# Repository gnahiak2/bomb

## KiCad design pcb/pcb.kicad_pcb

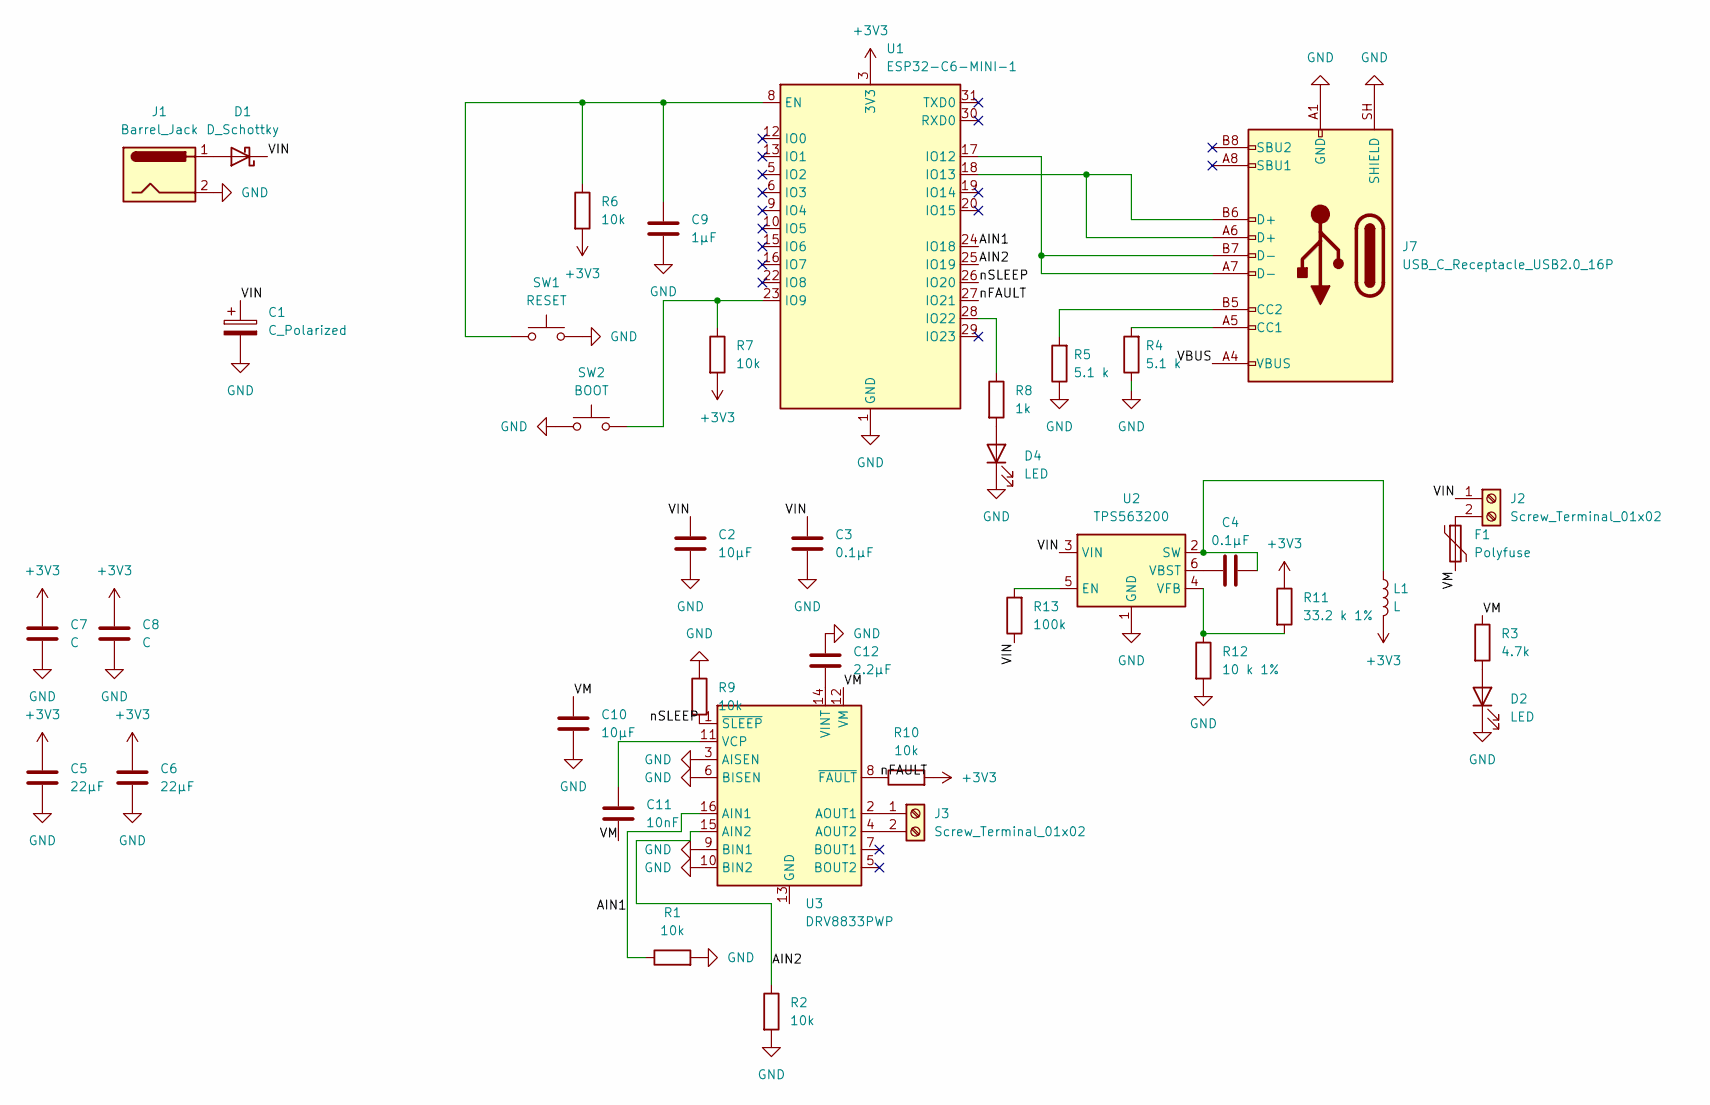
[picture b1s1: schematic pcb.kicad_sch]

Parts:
C1: C_Polarized; CP_Radial_D10.0mm_P5.00mm
C2, C10: 10µF; C_0805_2012Metric
C3, C4: 0.1µF; C_0805_2012Metric
C5, C6: 22µF; C_0805_2012Metric
C7, C8: C; C_0805_2012Metric
C9: 1µF; C_0805_2012Metric
C11: 10nF; C_0805_2012Metric
C12: 2.2µF; C_0805_2012Metric
D1: D_Schottky; D_SMA
D2, D4: LED; LED_0805_2012Metric
F1: Polyfuse; Fuse_1206_3216Metric
J1: Barrel_Jack; BarrelJack_Horizontal
J2, J3: Screw_Terminal_01x02; TerminalBlock_Phoenix_MKDS-1,5-2-5.08_1x02_P5.08mm_Horizont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
J7: USB_C_Receptacle_USB2.0_16P; USB_C_Receptacle_HRO_TYPE-C-31-M-12
L1: L; L_Sunlord_SWPA4030S
R1, R2, R6, R7, R9, R10: 10k; R_0805_2012Metric
R3: 4.7k; R_0805_2012Metric
R4, R5: 5.1 k; R_0805_2012Metric
R8: 1k; R_0805_2012Metric
R11: 33.2 k 1%; R_0805_2012Metric
R12: 10 k 1%; R_0805_2012Metric
R13: 100k; R_0805_2012Metric
SW1: RESET; SW_SPST_TL3342
SW2: BOOT; SW_SPST_TL3342
U1: ESP32-C6-MINI-1
U2: TPS563200; SOT-23-6
U3: DRV8833PWP; HTSSOP-16-1EP_4.4x5mm_P0.65mm_EP3.4x5mm_Mask2.46x2.31mm_The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

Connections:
+3V3: C5.1, C6.1, C7.1, C8.1, L1.2, R6.2, R7.2, R10.2, R11.1, U1.3 (3V3)
/AIN1: R1.1, U1.24 (IO18), U3.16 (AIN1)
/AIN2: R2.1, U1.25 (IO19), U3.15 (AIN2)
/VBUS: J7.A4 (VBUS), J7.A9 (VBUS), J7.B4 (VBUS), J7.B9 (VBUS)
/VIN: C1.1, C2.1, C3.1, D1.1 (K), J2.1, R13.1, U2.3 (VIN)
/VM: C10.1, C11.2, F1.2, R3.1, U3.12 (VM)
/nFAULT: R10.1, U1.27 (IO21), U3.8 (~FAULT)
/nSLEEP: R9.2, U1.26 (IO20), U3.1 (~SLEEP)
GND: C1.2, C2.2, C3.2, C5.2, C6.2, C7.2, C8.2, C9.2, C10.2, C12.1, D2.1 (K), D4.1 (K), J1.2, J7.A1 (GND), J7.A12 (GND), J7.B1 (GND), J7.B12 (GND), J7.SH (SHIELD), R1.2, R2.2, R4.1, R5.1, R9.1, R12.2, SW1.2, SW2.1, U1.1 (GND), U1.2 (GND), U1.11 (GND), U1.14 (GND), U1.36 (GND), U1.37 (GND), U1.38 (GND), U1.39 (GND), U1.40 (GND), U1.41 (GND), U1.42 (GND), U1.43 (GND), U1.44 (GND), U1.45 (GND), U1.46 (GND), U1.47 (GND), U1.48 (GND), U1.49 (GND), U1.50 (GND), U1.51 (GND), U1.52 (GND), U1.53 (GND), U2.1 (GND), U3.3 (AISEN), U3.6 (BISEN), U3.9 (BIN1), U3.10 (BIN2)
unnamed: D1.2 (A), J1.1
unnamed: D2.2 (A), R3.2
unnamed: D4.2 (A), R8.2
unnamed: F1.1, J2.2
unnamed: J3.1, U3.2 (AOUT1)
unnamed: J3.2, U3.4 (AOUT2)
unnamed: J7.A5 (CC1), R4.2
unnamed: J7.B5 (CC2), R5.2
unnamed: C9.1, R6.1, SW1.1, U1.8 (EN)
unnamed: R7.1, SW2.2, U1.23 (IO9)
unnamed: J7.A7 (D-), J7.B7 (D-), U1.17 (IO12)
unnamed: J7.A6 (D+), J7.B6 (D+), U1.18 (IO13)
unnamed: R8.1, U1.28 (IO22)
unnamed: R13.2, U2.5 (EN)
unnamed: C4.2, L1.1, U2.2 (SW)
unnamed: C4.1, U2.6 (VBST)
unnamed: R11.2, R12.1, U2.4 (VFB)
unnamed: U3.13 (GND), U3.17 (GND)
unnamed: C11.1, U3.11 (VCP)
unnamed: C12.2, U3.14 (VINT)

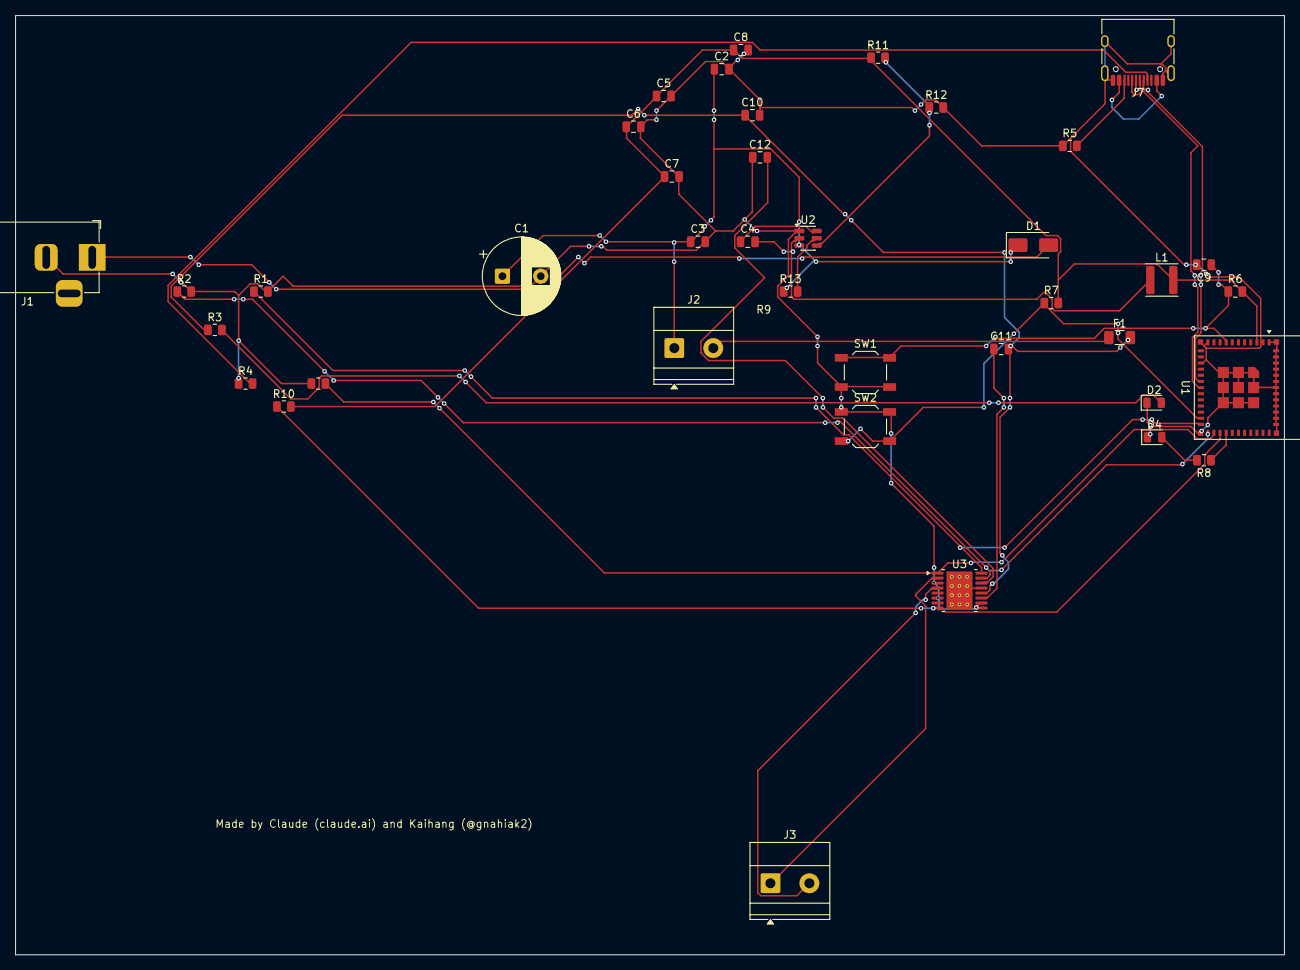
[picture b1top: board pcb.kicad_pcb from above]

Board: 2 copper layers, 165.5 x 122.5 mm, 39 parts (0 on the bottom side), 29 nets.
